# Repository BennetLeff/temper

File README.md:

# Temper — ESP32-S3 Induction Cooker

## Architecture

> Package inventory — boxes sized by lines of code, colored by language, with dependency arrows. The Mermaid diagram below shows data-flow relationships.

Temper is a consumer induction cooker built around three pillars: an
**ESP32-S3 firmware** with an 8-state transition-table machine handling
real-time power control and hardware-latched protection circuits; a **KiCad
PCB design** optimized through a custom CP-SAT-based signal-integrity and
thermal-aware placer pipeline; and a **Python/Rust placer toolchain**
(CP-SAT solver, geometry/DRC/DSN/IPC crates, workflow DAG) that automates layout
and checks placement against IPC standards. Protection — over-current,
over-voltage, thermal shutdown, UVLO — is *designed* to be hardware-latched with
firmware monitoring.

> **Implementation status is deliberately not summarized here.** As of this
> writing not all protection gates are implemented, and none has been validated
> on hardware. [`docs/STRATEGY.md`](docs/STRATEGY.md) holds the measured state
> and the gate matrix; it churns by design, and this file does not restate it.
> An earlier version of this paragraph asserted that all safety gates were
> hardware-latched and monitored, which was not true when written.

```mermaid
graph TD
  subgraph Firmware ["Firmware (ESP32-S3, C)"]
    SM[8-State Machine]
    PROT[Protection Circuits<br/>OCP OVP THM UVLO]
  end

  subgraph PCB ["PCB (KiCad)"]
    KICAD[Schematics & Layout]
  end

  subgraph Placer ["Placer (Python + Rust)"]
    CPSAT[CP-SAT Solver]
    RUST[Rust Crates<br/>Geometry DRC DSN IPC PCL-IR]
  end

  subgraph Pipeline ["Pipeline & CI"]
    DAG[temper-workflow DAG]
    REGR[Placer Regression]
    FW[Firmware Tests]
    PY[Python Tests]
  end

  SM --> PROT
  CPSAT --> RUST
  KICAD --> DAG
  RUST --> DAG
  DAG --> REGR
  FW --> DAG
  PY --> DAG
```

## Get Started in 60 Seconds

Build and run the firmware test suite:

```bash
cmake -B firmware/test/build firmware/test
cmake --build firmware/test/build
./firmware/test/build/test_state_machine_only
```

Or build and test the placer toolchain:

```bash
uv sync
uv run pytest packages/temper-placer/tests/
```

**Prerequisites:** CMake ≥ 3.16 and the ESP-IDF toolchain (see
[CONTRIBUTING.md](CONTRIBUTING.md) for full setup instructions).

## Reading Paths

### 5-Minute Overview

For anyone wanting to understand what Temper is and how it's structured:

- [docs/STRATEGY.md](docs/STRATEGY.md) — project approach, safety and performance gates
- Architecture diagram above — subsystem relationships at a glance
- [Project structure](#project-structure) — what lives where

### 30-Minute Build & Test

For developers ready to build, test, and navigate the codebase:

- [CONTRIBUTING.md](CONTRIBUTING.md) — development workflow, commit convention, codegen rules
- [AGENTS.md](AGENTS.md) — firmware build section; codegen and CI conventions
- [`.importlinter`](.importlinter) — package boundary contracts; verify with `uv run python scripts/import_linter_gate.py`
- [packages/temper-placer/tests/regression/](packages/temper-placer/tests/regression/) — placer regression test suite

### Deep-Dive Contributor

For contributors working on architecture, verification, or toolchain internals:

- [AGENTS.md](AGENTS.md) — full agent instructions, traceability convention, physics verification rules
- [docs/plans/](docs/plans/) — feature and improvement plans with requirements trace
- [docs/solutions/](docs/solutions/) — documented fixes for past bugs, patterns, and tooling decisions
- [docs/TRACEABILITY.md](docs/TRACEABILITY.md) — requirements-to-code traceability specification
- [docs/physics-verification-methodology.md](docs/physics-verification-methodology.md) — CP-SAT constraint soundness and validation framework

## Project Structure

<!-- BEGIN GENERATED: repo-map -- edits here are overwritten by scripts/gen_repo_state.py -->

*All 22 tracked top-level directories. Generated -- a new directory without a description fails CI.*

| Directory | Purpose |
|---|---|
| `.cargo/` | Cargo config -- macOS pyo3 `-undefined dynamic_lookup` link flags |
| `.github/` | CI workflows, issue templates, code owners |
| `benchmarks/` | CP-SAT benchmark harness and external board corpora manifests |
| `ci-corpus/` | Gate-mutation-testing corpus (canaries + mutations.yaml) for CI gates |
| `components/` | Local KiCad symbol/footprint libraries, one directory per part |
| `configs/` | Named placer configurations (deterministic, production) |
| `crates/` | Rust-only crates -- no pyproject.toml, outside the uv workspace. Where code lives once it no longer needs an interpreter: the temper binary and the CP-SAT FFI |
| `dashboard/` | Static HTML/JS dashboard for placer metrics |
| `datasheets/` | Vendor PDFs for parts used in the design |
| `docs/` | Plans, brainstorms, solutions, evidence, specs, and strategy |
| `elec/` | Atopile electrical source -- the schematic's source of truth |
| `firmware/` | ESP32-S3 firmware (C), 8-state machine and protection monitoring |
| `instruments/` | Measurement instrument designs, calibration procedures, and prototype fabrication files |
| `max31865/` | KiCad library for the MAX31865 RTD front-end (predates components/) |
| `metrics/` | Recorded routing/placement metric snapshots (JSON) |
| `output_gerbers/` | Exported Gerber/drill artifacts from a past routed revision |
| `packages/` | Python and Rust workspace members -- placer, DRC, geometry, router |
| `pcb/` | KiCad project: schematics, board, and project settings |
| `power_pcb_dataset/` | Regression corpus, baselines, and DRC ceilings |
| `scripts/` | CI gates, generators, and one-off analysis tooling |
| `simulation/` | ngspice models and protection-gate simulation harnesses |
| `tools/` | Developer utilities not wired into CI gates |

<!-- END GENERATED: repo-map -->

## Inventory

<!-- BEGIN GENERATED: inventory -- edits here are overwritten by scripts/gen_repo_state.py -->

**18 workspace packages** under `packages/`:

- `temper-constraint-compiler`
- `temper-data-model`
- `temper-design-bundle`
- `temper-drc-rs`
- `temper-geometry`
- `temper-io-types`
- `temper-orchestration`
- `temper-pcl-ir`
- `temper-placer`
- `temper-py-bridge`
- `temper-py-bridge-derive`
- `temper-quality-oracle`
- `temper-rust-router`
- `temper-rust-router-core`
- `temper-thermal`
- `temper-wasm-test-runner`
- `temper-worker`
- `temper-workflow`

Sizes and dependency edges are in [`ARCHITECTURE.svg`](./ARCHITECTURE.svg), regenerated automatically on push.

<!-- END GENERATED: inventory -->

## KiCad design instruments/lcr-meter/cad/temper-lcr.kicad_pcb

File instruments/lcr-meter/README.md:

# Temper LCR meter — revision F, based on TI TIDA-060029

A single **100 × 100 mm, four-layer PCB** (Rev F: the Rev E circuit re-laid by hand for a 110 × 110 × 36 mm box, see [rev-f-before-after](docs/rev-f-before-after.md); Rev E was 140 × 105 mm, Rev D 140 × 100 mm) for small-signal bench measurements of isolated, discharged stage53 components. It retains the TI OPA2810 source buffer, voltage-sense followers and transimpedance circuit, including matched 100 Ω / 5 kΩ / 100 kΩ source and feedback resistors. Revision C introduced one short, local 100 pF feedback capacitor on every range and corrected the ADC-driver compensation using TI’s evaluation-board circuit. Revision D adds a 22 Ω isolation resistor (R94) between the LO terminal and the TIA summing node, so cable and fixture capacitance no longer erode the 100 Ω range's stability. It also adds ±12 V rail monitors that the firmware reports, 1 Ω LDO input resistors and a VNEG trim. See the [Rev D decision](docs/rev-d-decision.md). Excitation, simultaneous acquisition, power and USB control are integrated on the same board. Rev F adds an orange front-panel status light (lit during a capture) and six lid-off debug LEDs: 5V, 3V3, +12, −12, firmware heartbeat (HB) and fault (FLT); [bring-up-rev-e.md](docs/bring-up-rev-e.md) §1a lists what each shows.

**Engineering prototype — design and manufacturing files complete.** Native KiCad ERC/DRC, connectivity, schematic parity and BOM/placement checks pass. No board has been fabricated, calibrated or physically validated. TI's reference accuracy does not transfer automatically to this implementation. No files have been uploaded to a manufacturer and no order has been placed.

- [Circuit PDF](previews/schematic.pdf) and [native KiCad project](cad/temper-lcr.kicad_pro).
- [TI reference conformance](docs/reference-conformance.md): retained, changed and added circuits, and physical layout review evidence.
- [Bring-up procedure](docs/bring-up.md), [full-chain simulation evidence](docs/analog-validation-rev-c.md), [Rev D decision and in-box studies](docs/rev-d-decision.md), [cost estimate](docs/cost-estimate.md).
- [Firmware](firmware/README.md) and [Rust host CLI](host/README.md), including prebuilt RP2040 UF2 and macOS ARM64 host binary.
- [Complete revision F package](temper-lcr-rev-f-package.zip), [Gerber/drill ZIP](manufacturing/temper-lcr-gerbers.zip), [fabrication instructions](manufacturing/FABRICATION.md), and [verification receipt](validation/README.md). The BOM and CPL reside in `manufacturing/`.

The board requires **filled, copper-capped, planarized via-in-pad fabrication**. Budget approximately **$320–450 for the minimum prototype assembly batch, plus the vendor's unquoted four-layer via-in-pad surcharge**; fitted components alone are about $76 per board. JLC's minimum batch is five bare boards and two assembled boards, even when only one working instrument is needed. See the cost estimate for inclusions and limits.

## Circuit and operation

AD9833 sine generator → two-stage RC reconstruction → AC coupling and OPA810 gain 6 → retained TIDA-060029 analog core → two THS4551 differential drivers → ADS9224R simultaneous 16-bit ADC → RP2040 USB CDC. The 24 MHz DDS clock derives from the MCU; acquisition uses two serial data lanes at 1 MSPS, and the firmware boxcar-sums 1–20 consecutive conversions per output sample at low frequencies instead of undersampling. The Rust host fits both waveforms at the actual DDS frequency, applies complex feedback impedance and fixture calibration, and reports complex impedance and equivalent series L/C/R.

Revision E takes power and data from **one USB-C cable**: U16 (TPS2553) switches VBUS onto the 5 V rail with soft start and a 1.0–1.16 A current limit. A USB-C port or a USB 3 port (900 mA) supplies the estimated 0.45 A; a USB 2.0 type-A port (500 mA) is marginal. Revision D and earlier used a regulated 5 V, 1 A, center-positive external supply, with USB for data and ground. A forced-PWM TPS65131 and low-noise positive/negative postregulators supply approximately ±12 V. The instrument is ground referenced; it has no mains isolation. Neither DUT terminal should be connected to an external powered circuit.

With power removed, fit exactly one matched pair of removable jumpers:

| Range | Source selection | Feedback selection | Feedback impedance |
|---|---|---|---|
| Low | JP1 | JP4 | 22 Ω + (100 Ω with local 100 pF) |
| Medium | JP2 | JP5 | 22 Ω + (5 kΩ with local 100 pF) |
| High | JP3 | JP6 | 22 Ω + (100 kΩ with local 100 pF) |

The first qualification targets are 35–60 kHz stage53 coil and resonant-capacitor measurements, plus a 1.5 kHz bus-capacitor check. The host's measurement grid is 1.5, 35.5, 40.5, 50.5 and 60.5 kHz: it refuses whole-kHz frequencies, where USB start-of-frame lines and aliased DDS harmonics land in the fit, and pairs each capture with a source-off record (see `host/README.md` and `validation/power-spurs/`). The firmware permits 100 Hz–100 kHz excitation, but usable accuracy and impedance limits must be established with standards at each frequency and range. Maximum nominal source is approximately 3.6 Vpp; the 100 Ω source resistor plus R94 limit short-circuit current to approximately 15 mA peak. This justifies omitting TI's optional BUF634A stages for this small-signal use.

## Stage53 measurements

| Component | Intended check | Practical limit |
|---|---|---|
| Coil, with and without pan | Complex impedance and equivalent series L/R at 35–60 kHz, roughly 5–30 Ω | Small-signal only; does not predict power-level loss, heating or saturation |
| Five 100 nF capacitors / 0.5 µF bank | Individual values, bank impedance and relative loss comparisons | Calibrated ESR uncertainty must be measured; no milliohm claim |
| 9 µF bus capacitors | Capacitance around 1.5 kHz, approximately 11.8 Ω | Discharge and isolate first; no high-voltage or high-frequency ESR qualification |
| Chokes, snubber/gate capacitors | Value comparison and gross faults within qualified ranges | Parallel circuit paths require disconnection or lifting a lead |
| 1 mΩ current shunt | Unsupported | Requires a separate four-wire low-resistance measurement architecture |

Stage53 source: `worktrees/runs-native21/s53/c53int/section.kicad_pcb`, SHA256 `82af7bd93e62d1f2e6c7c2c2b971a4830bf6e09078bae3f269d8bead9a31fd27`. The LCR project does not modify or release the Temper power-stage board.

## Reproduction and qualification

Explicit component/pin/placement records are in `cad/design.json`; routed segments, vias, plane and keepouts are in `cad/routing.json`. The existing Python adapter calls native pcbnew and serializes KiCad sources. Host measurement logic is Rust; RP2040 firmware uses the official Pico SDK. `cad/rebuild.sh` regenerates native CAD, fills zones, fails on ERC/DRC findings, exports fabrication data and verifies source/schematic/PCB/BOM/placement parity. KiCad 10.0.4 was used; project-local symbols and footprints are included.

Hardware qualification remains essential: inspect rails and oscillation, check source settling, acquire a source-off noise sweep, calibrate with known standards and verify a third independent standard. The full coupled amplifier models now converge at a checked true DC operating point. Bilateral loop measurements, independent controlled-source cuts, two FDA models, tolerance/load sweeps and local fast disturbances support the revised compensation. These typical-model checks do not establish physical-board stability or calibrated accuracy; all three ranges still require scope qualification. Revision D-riso22 firmware and host reject revision C and earlier calibration files, and refuse to measure with either analog rail out of window. The high range favors frequencies up to 10 kHz for sensitivity; its 100 pF feedback pole is 15.9 kHz. Final JLCPCB placement preview and assembler DFM remain outstanding.

Revision A’s AD5933 implementation and revision B’s uncompensated TI derivative are preserved under `archive/rev-a/` and `archive/rev-b/`. Both are superseded. Revision C (no R_iso) is superseded by D; its snapshot is commit ff1ffb45b. Order only from the revision D package and its current BOM/CPL. Historical simulation files are labelled separately and are not the manufacturing target.

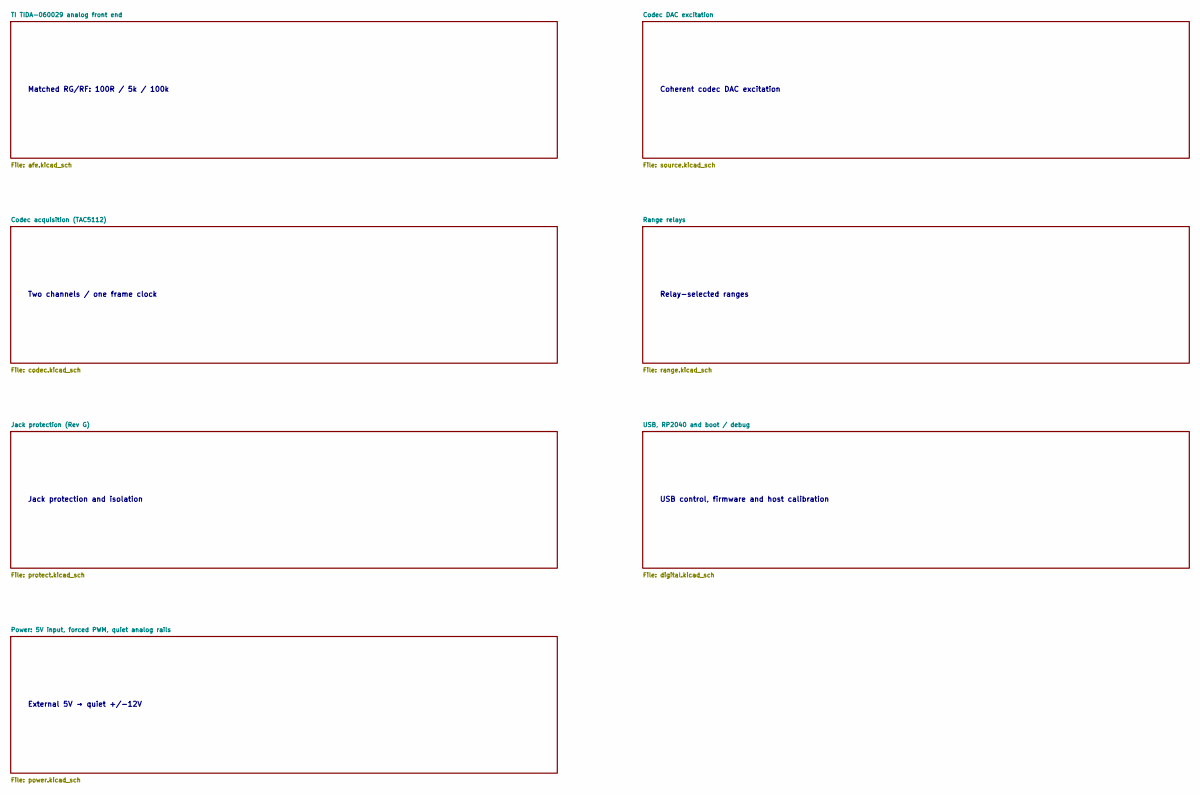
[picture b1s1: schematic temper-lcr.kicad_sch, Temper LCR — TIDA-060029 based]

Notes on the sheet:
Matched RG/RF: 100R / 5k / 100k
Coherent codec DAC excitation
Two channels / one frame clock
Relay-selected ranges
Jack protection and isolation
USB control, firmware and host calibration
External 5V → quiet +/-12V

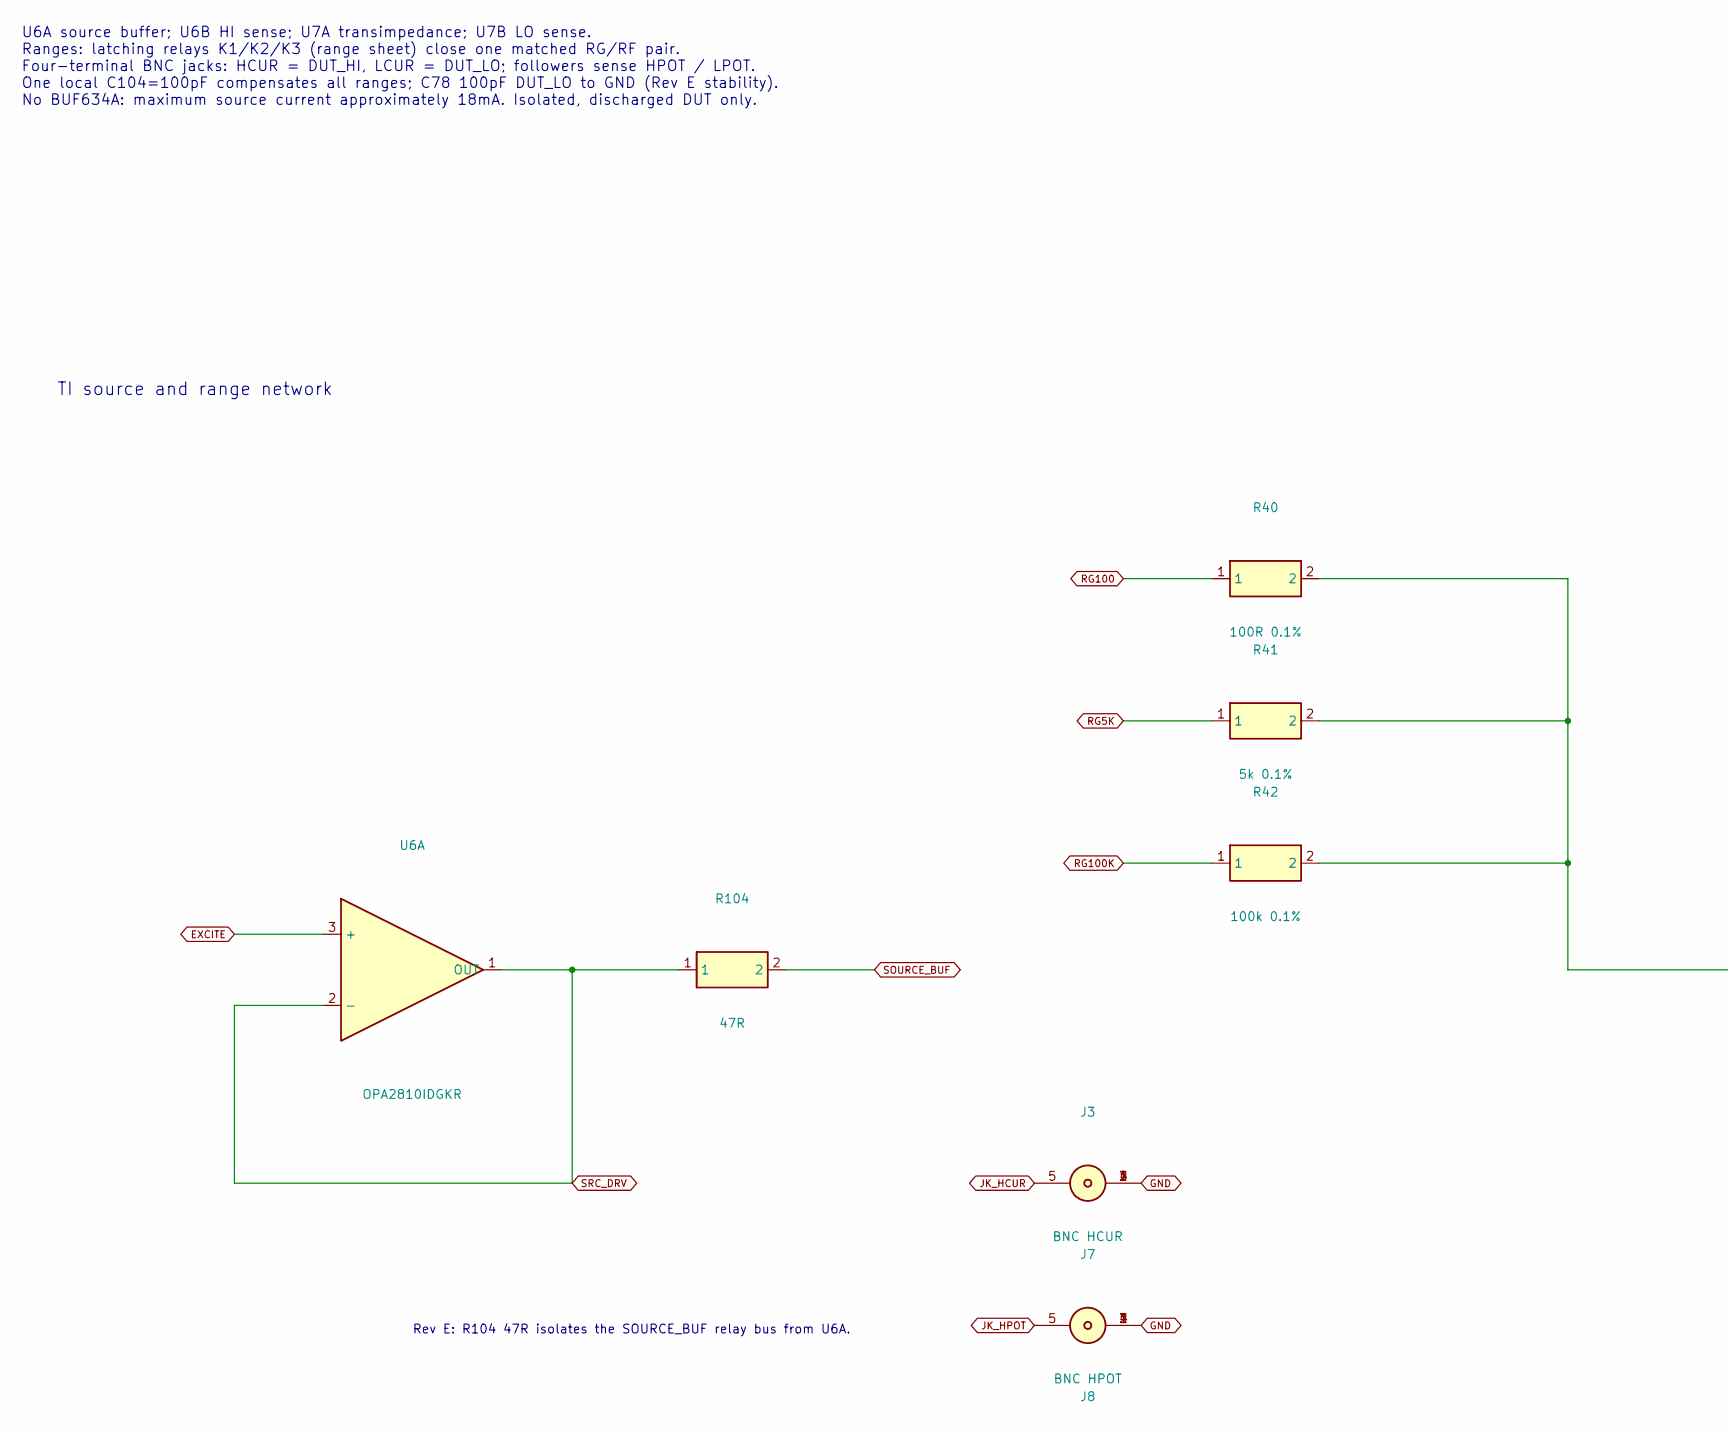
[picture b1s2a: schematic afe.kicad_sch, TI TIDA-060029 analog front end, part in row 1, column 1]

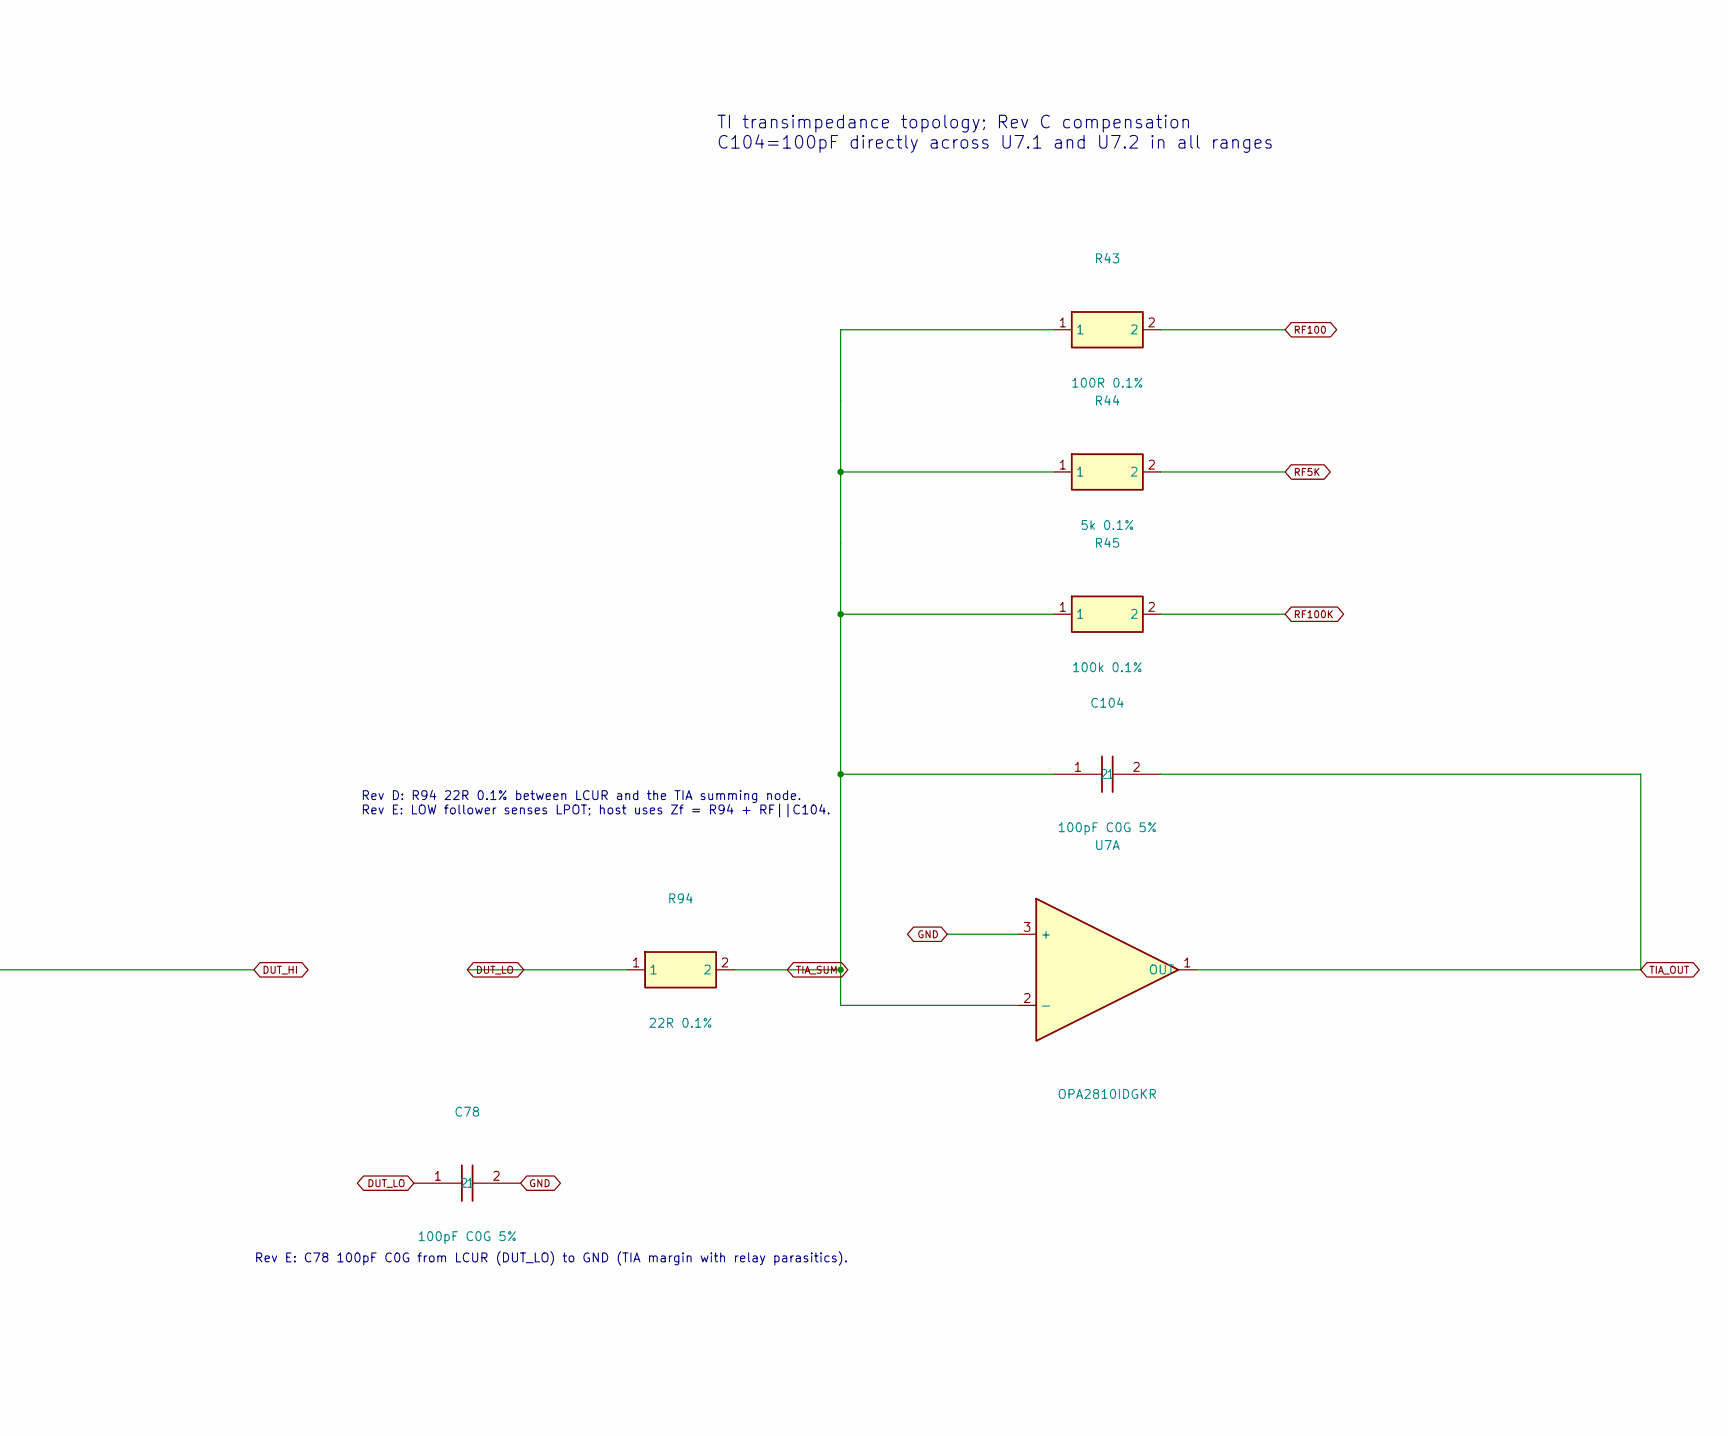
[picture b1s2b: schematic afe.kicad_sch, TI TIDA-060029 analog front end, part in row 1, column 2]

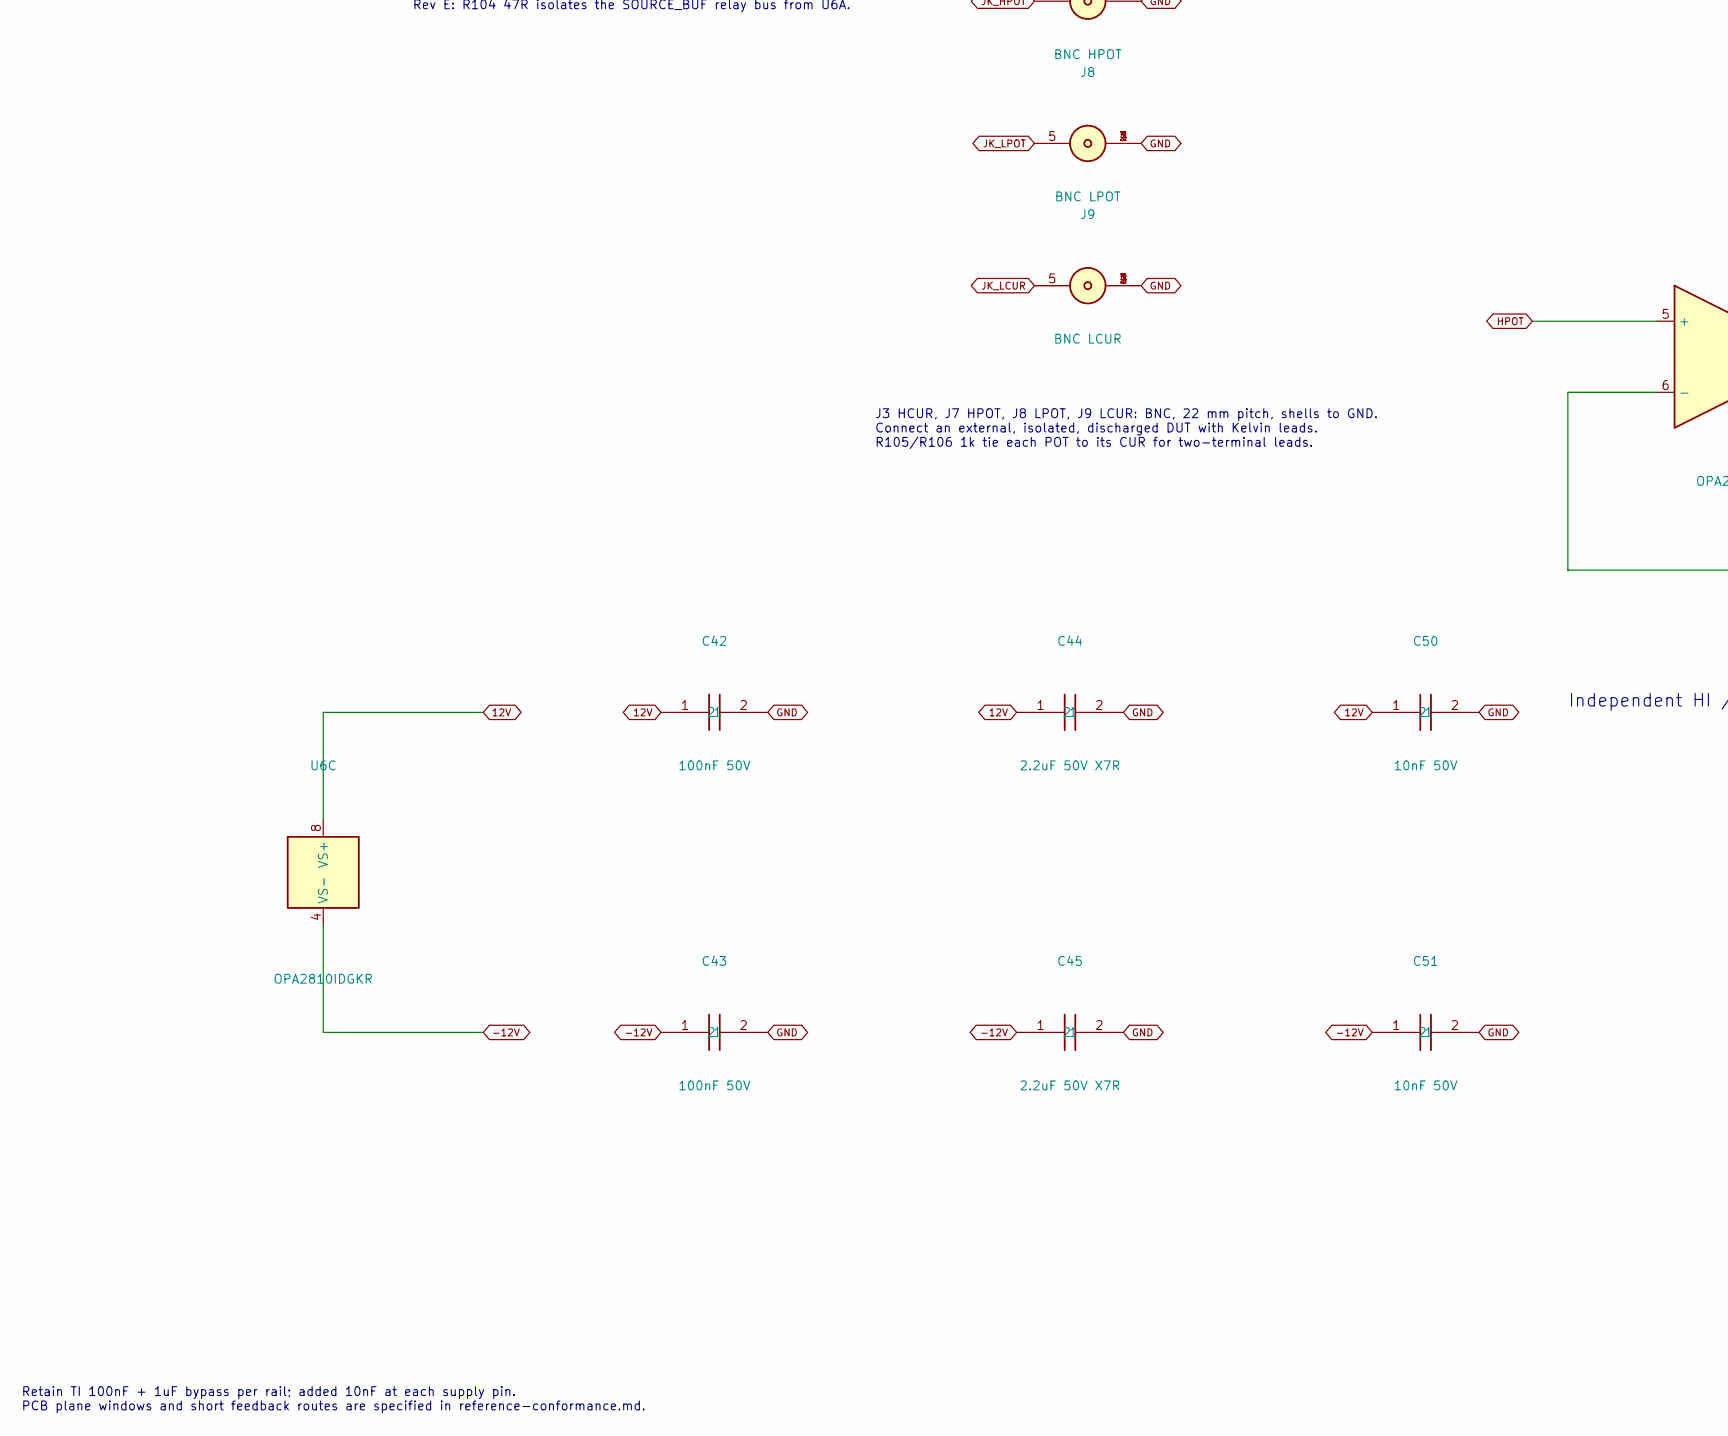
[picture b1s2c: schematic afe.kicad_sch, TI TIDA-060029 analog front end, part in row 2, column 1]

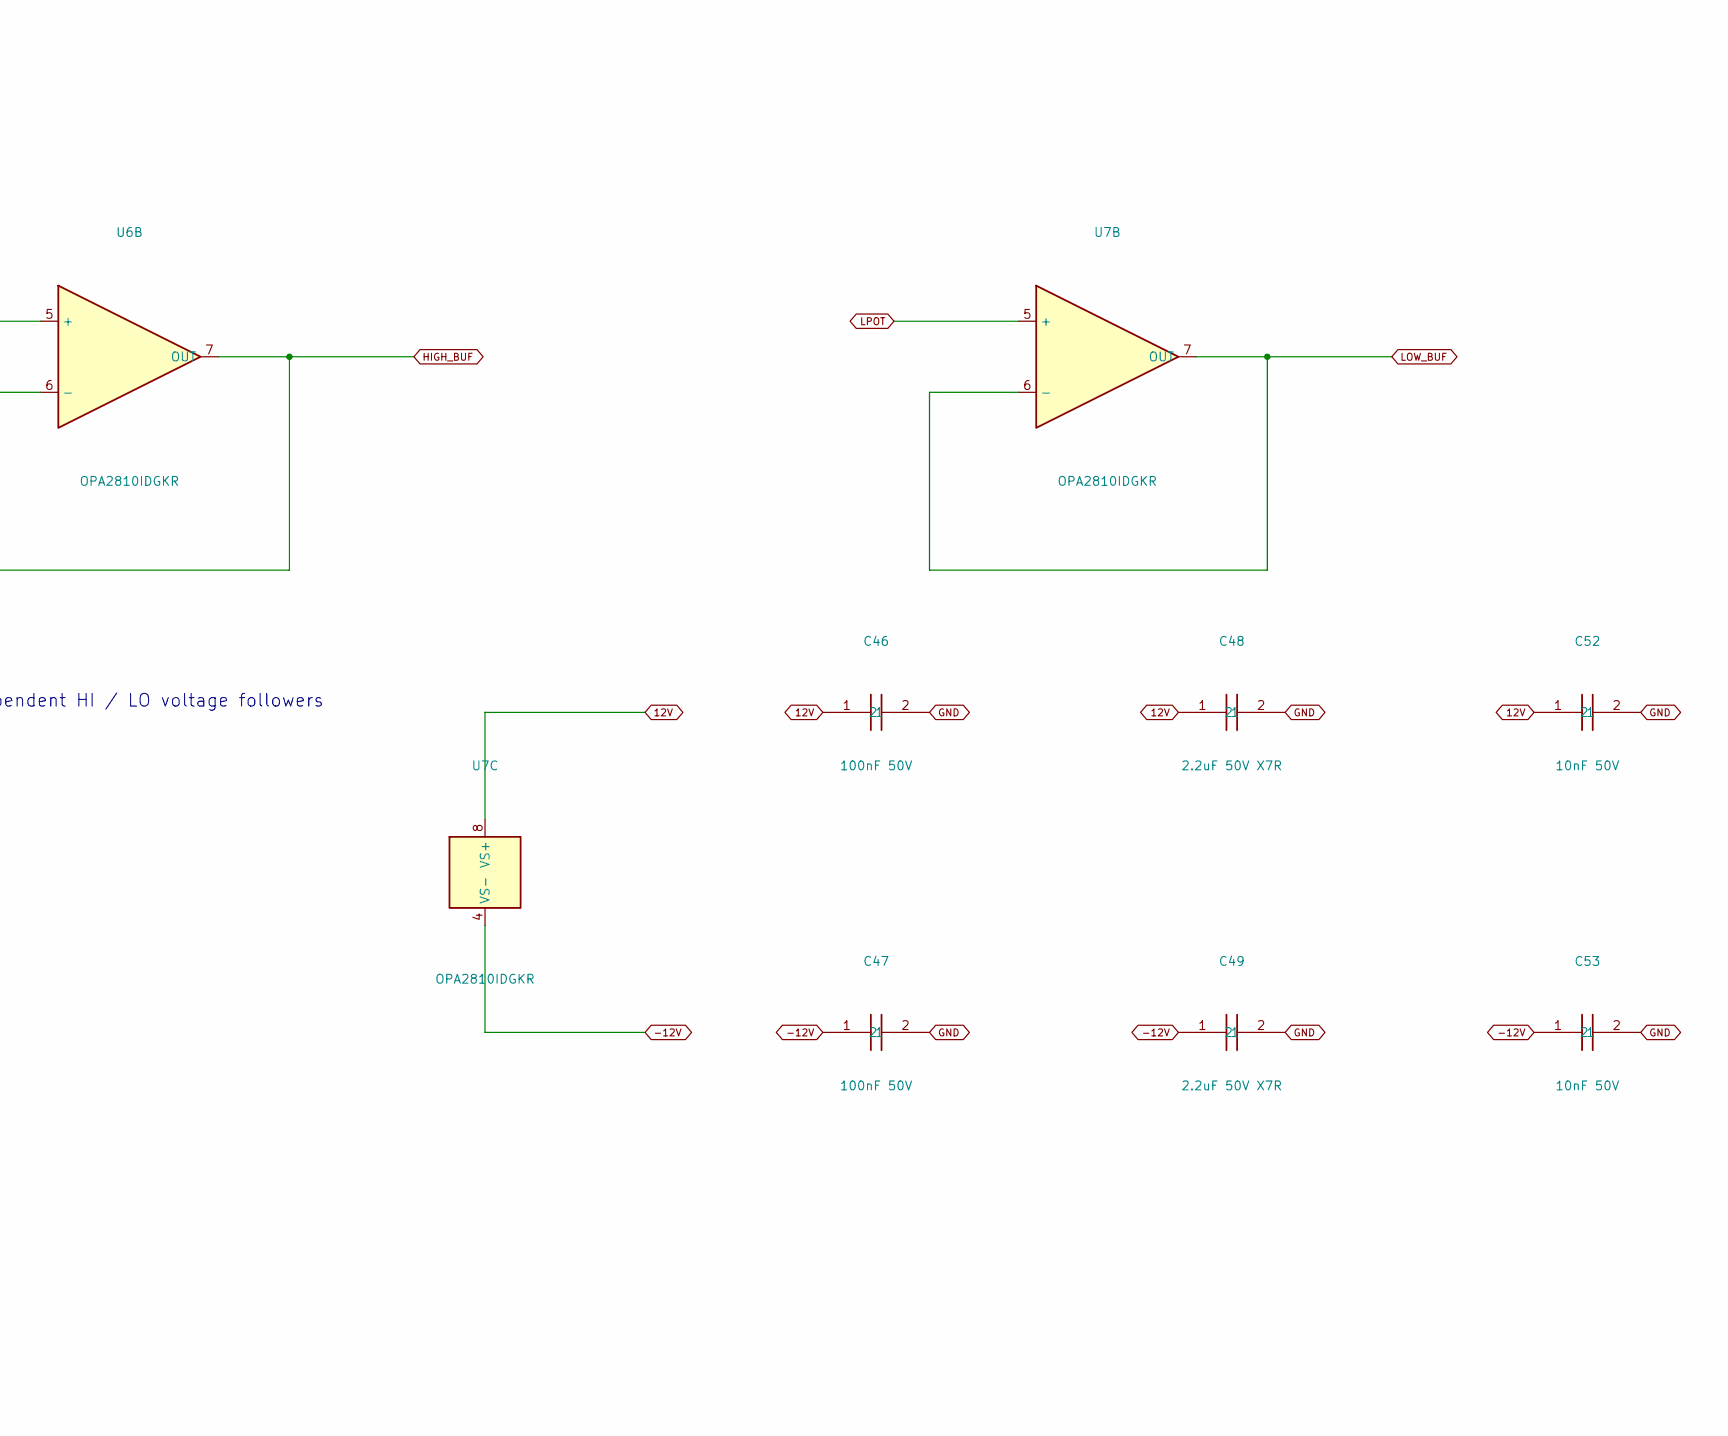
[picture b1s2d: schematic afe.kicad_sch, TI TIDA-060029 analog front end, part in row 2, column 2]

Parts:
C42, C43, C46, C47: 100nF 50V; C_0603_1608Metric; MPN CC0603KRX7R9BB104; LCSC C14663
C44, C45, C48, C49: 2.2uF 50V X7R; C_0805_2012Metric; MPN CC0805KKX7R9BB225; LCSC C125847
C50, C51, C52, C53: 10nF 50V; C_0603_1608Metric; MPN 0603B103K500NT; LCSC C57112
C78, C104: 100pF C0G 5%; C_0603_1608Metric; MPN CL10C101JB8NNNC; LCSC C14858
J3: BNC HCUR; BNC_SAMZO_KYWE-295-W4-N_Horizontal; MPN BNC-KYWE-295-W4-N; LCSC C41416668
J7: BNC HPOT; BNC_SAMZO_KYWE-295-W4-N_Horizontal; MPN BNC-KYWE-295-W4-N; LCSC C41416668
J8: BNC LPOT; BNC_SAMZO_KYWE-295-W4-N_Horizontal; MPN BNC-KYWE-295-W4-N; LCSC C41416668
J9: BNC LCUR; BNC_SAMZO_KYWE-295-W4-N_Horizontal; MPN BNC-KYWE-295-W4-N; LCSC C41416668
R40, R43: 100R 0.1%; R_0603_1608Metric; MPN RT0603BRD07100RL; LCSC C122970
R41, R44: 5k 0.1%; R_0603_1608Metric; MPN AR03BTCX5001; LCSC C2828621
R42, R45: 100k 0.1%; R_0603_1608Metric; MPN RT0603BRD07100KL; LCSC C122538
R94: 22R 0.1%; R_0603_1608Metric; MPN RT0603BRD0722RL; LCSC C861239
R104: 47R; R_0603_1608Metric; MPN 0603WAF470JT5E; LCSC C23182
U6, U7: OPA2810IDGKR; VSSOP-8_3x3mm_P0.65mm; MPN OPA2810IDGKR; LCSC C2864204

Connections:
12V: C42.1, C44.1, C46.1, C48.1, C50.1, C52.1, U6.8 (VS+), U7.8 (VS+); also elsewhere on the board
-12V: C43.1, C45.1, C47.1, C49.1, C51.1, C53.1, U6.4 (VS-), U7.4 (VS-); also elsewhere on the board
DUT_HI: R40.2, R41.2, R42.2; also elsewhere on the board
DUT_LO: C78.1, R94.1; also elsewhere on the board
EXCITE: U6.3 (+); also elsewhere on the board
GND: C42.2, C43.2, C44.2, C45.2, C46.2, C47.2, C48.2, C49.2, C50.2, C51.2, C52.2, C53.2, C78.2, J3.1, J3.2, J3.3, J3.4, J7.1, J7.2, J7.3, J7.4, J8.1, J8.2, J8.3, J8.4, J9.1, J9.2, J9.3, J9.4, U7.3 (+); also elsewhere on the board
HIGH_BUF: U6.6 (-), U6.7 (OUT); also elsewhere on the board
HPOT: U6.5 (+); also elsewhere on the board
JK_HCUR: J3.5; also elsewhere on the board
JK_HPOT: J7.5; also elsewhere on the board
JK_LCUR: J9.5; also elsewhere on the board
JK_LPOT: J8.5; also elsewhere on the board
LOW_BUF: U7.6 (-), U7.7 (OUT); also elsewhere on the board
LPOT: U7.5 (+); also elsewhere on the board
RF5K: R44.2; also elsewhere on the board
RF100: R43.2; also elsewhere on the board
RF100K: R45.2; also elsewhere on the board
RG5K: R41.1; also elsewhere on the board
RG100: R40.1; also elsewhere on the board
RG100K: R42.1; also elsewhere on the board
SOURCE_BUF: R104.2; also elsewhere on the board
SRC_DRV: R104.1, U6.1 (OUT), U6.2 (-)
TIA_OUT: C104.2, U7.1 (OUT); also elsewhere on the board
TIA_SUM: C104.1, R43.1, R44.1, R45.1, R94.2, U7.2 (-)

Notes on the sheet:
U6A source buffer; U6B HI sense; U7A transimpedance; U7B LO sense. Ranges: latching relays K1/K2/K3 (range sheet) close one matched RG/RF pair. Four-terminal BNC jacks: HCUR = DUT_HI, LCUR = DUT_LO; followers sense HPOT / LPOT. One local C104=100pF compensates all ranges; C78 100pF DUT_LO to GND (R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
TI source and range network
Rev E: R104 47R isolates the SOURCE_BUF relay bus from U6A.
J3 HCUR, J7 HPOT, J8 LPOT, J9 LCUR: BNC, 22 mm pitch, shells to GND. Connect an external, isolated, discharged DUT with Kelvin leads. R105/R106 1k tie each POT to its CUR for two-terminal leads.
Rev D: R94 22R 0.1% between LCUR and the TIA summing node. Rev E: LOW follower senses LPOT; host uses Zf = R94 + RF||C104.
Rev E: C78 100pF C0G from LCUR (DUT_LO) to GND (TIA margin with relay parasitics).
TI transimpedance topology; Rev C compensation C104=100pF directly across U7.1 and U7.2 in all ranges
Independent HI / LO voltage followers
Retain TI 100nF + 1uF bypass per rail; added 10nF at each supply pin. PCB plane windows and short feedback routes are specified in reference-conformance.md.

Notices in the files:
README.md:
License: proprietary
